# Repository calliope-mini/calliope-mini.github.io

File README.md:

# Technical Documentation

[see here](https://calliope-mini.github.io)

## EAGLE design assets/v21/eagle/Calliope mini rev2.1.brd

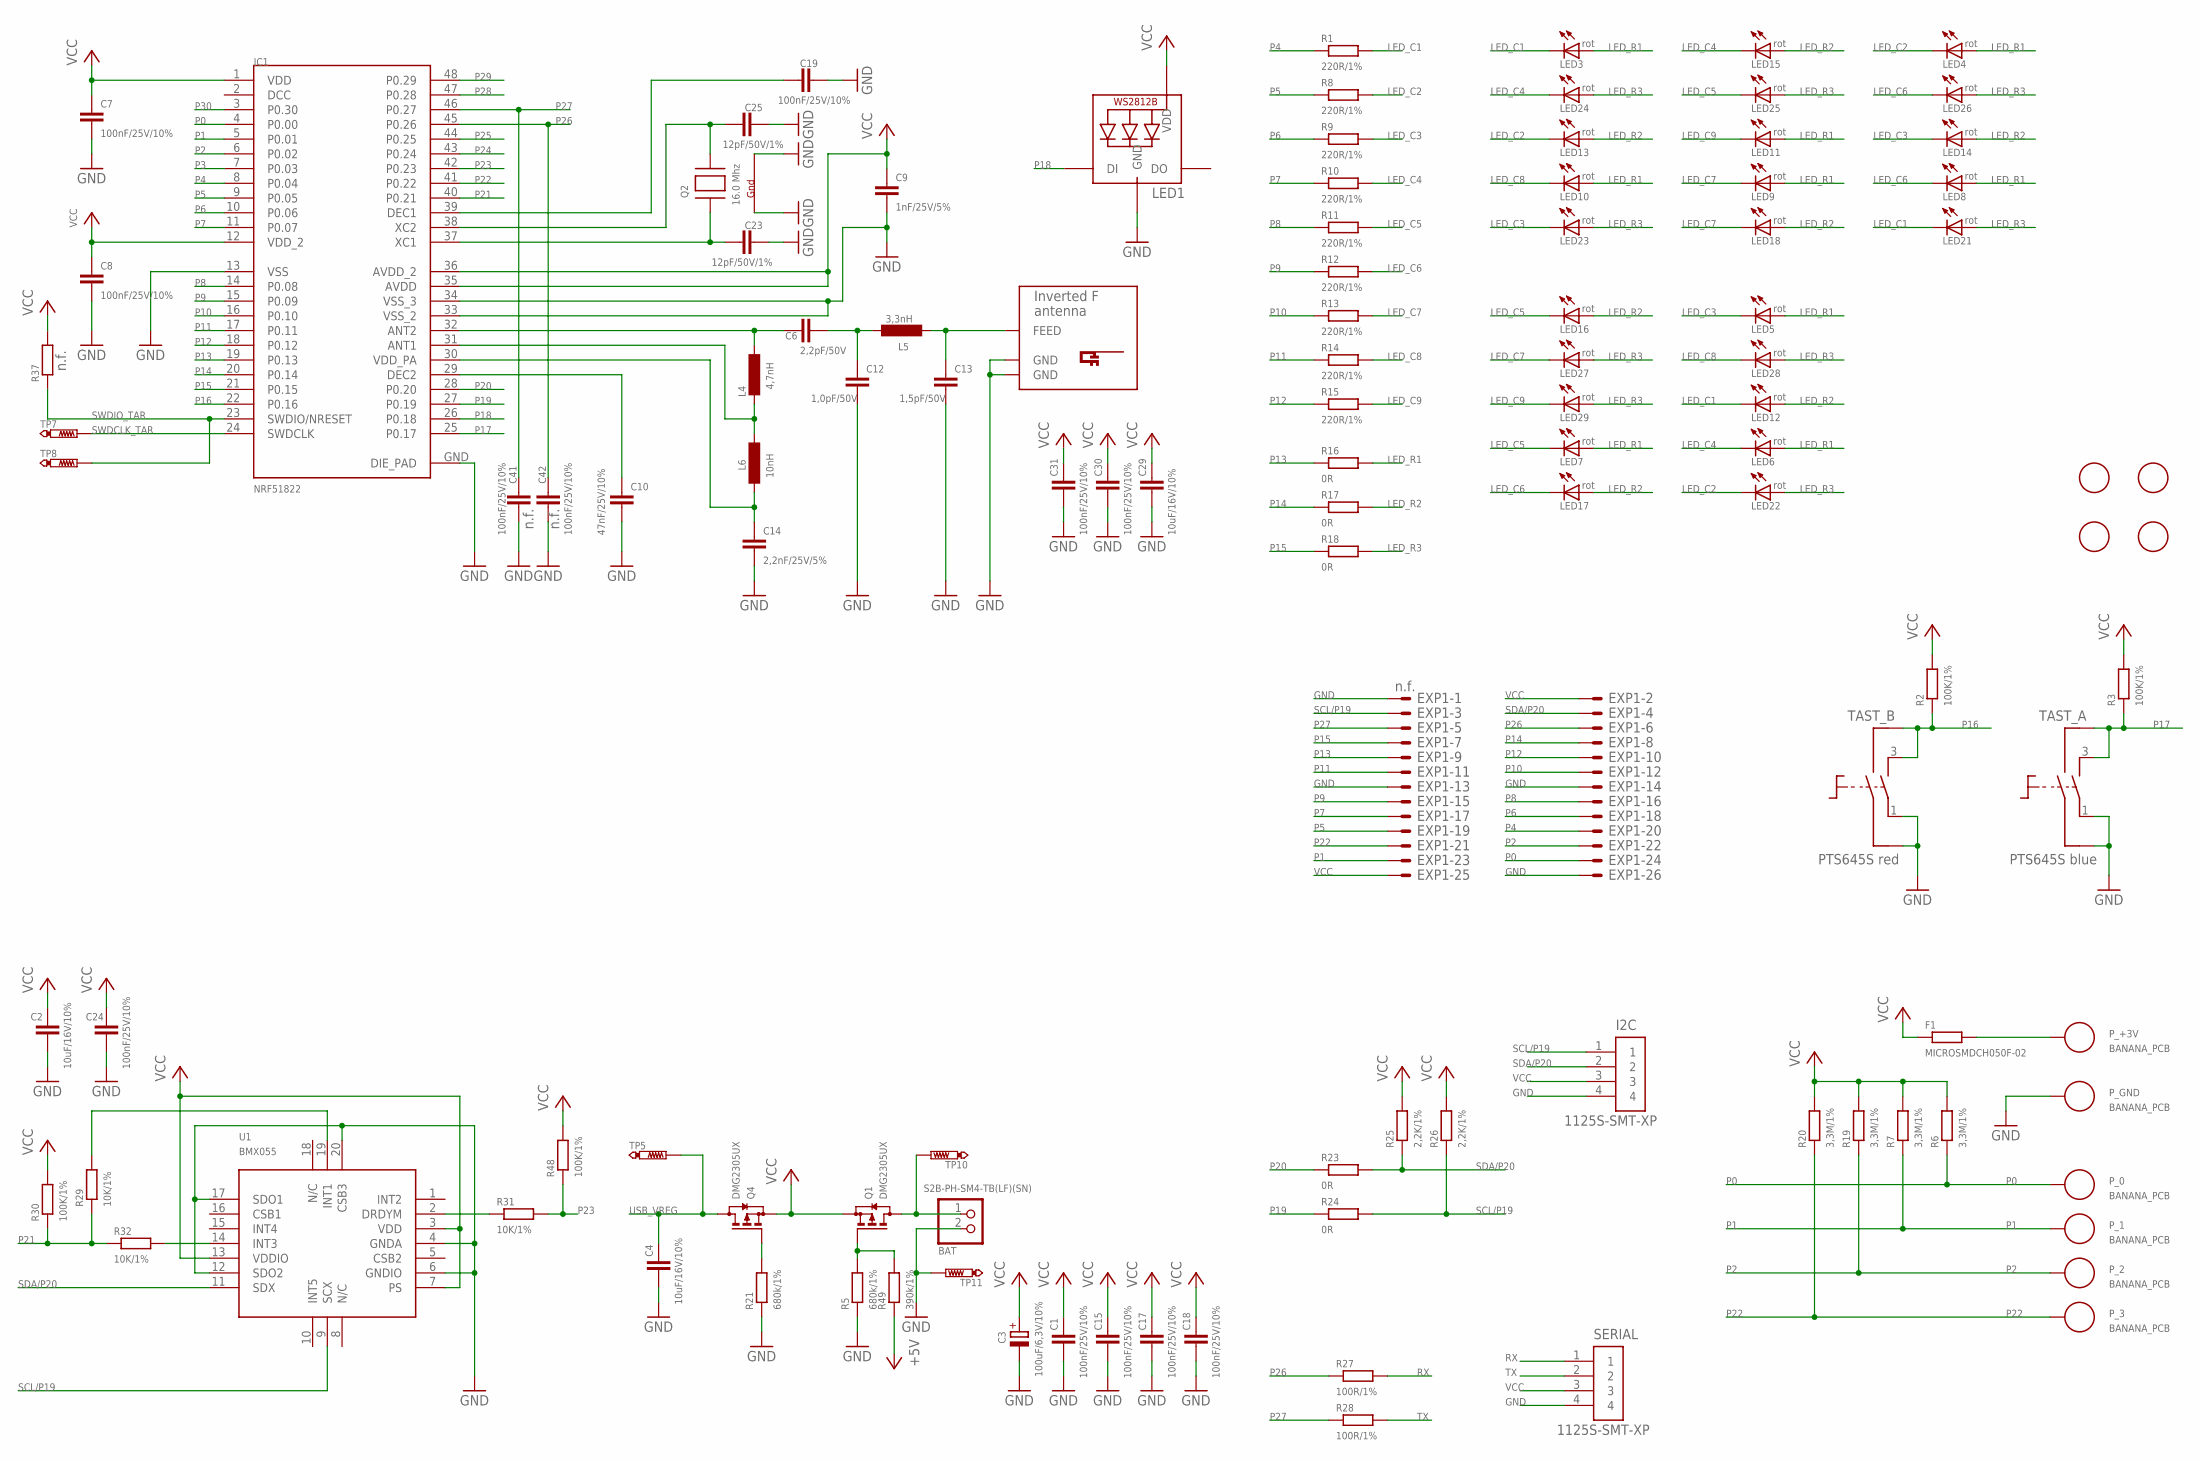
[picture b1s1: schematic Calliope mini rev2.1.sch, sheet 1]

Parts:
BAT: S2B-PH-SM4-TB(LF)(SN); JST-PH-2-SMT-RA
C1, C7, C8, C15, C17, C18, C19, C24, C30, C31, C41, C42: 100nF/25V/10%; 0402
C2, C4, C29: 10uF/16V/10%; 0402
C3: 100uF/6,3V/10%; D/7343-31R
C6: 2,2pF/50V; 0402
C9: 1nF/25V/5%; 0402
C10: 47nF/25V/10%; 0402
C12: 1,0pF/50V; 0402
C13: 1,5pF/50V; 0402
C14: 2,2nF/25V/5%; 0402
C23, C25: 12pF/50V/1%; 0402
EXP1: ML26E; ML26
F1: MICROSMDCH050F-02; R1210
I2C: 1125S-SMT-XP
IC1: NRF51822; QFN48
L4: 4,7nH; 0402
L5: 3,3nH; 0402
L6: 10nH; 0402
LED1: SK6812MINI; LED3535
LED3, LED4, LED5, LED6, LED7, LED8, LED9, LED10, LED11, LED12, LED13, LED14, LED15, LED16, LED17, LED18, LED21, LED22, LED23, LED24, LED25, LED26, LED27, LED28, LED29: rot; CHIPLED_0603
P_0, P_1, P_2, P_3: BANANA_PCB; BANANA_REC
P_+3V: BANANA_PCB; BANANA_REC
P_GND: BANANA_PCB; BANANA_REC
Q1, Q4: DMG2305UX; SOT23
Q2: 16.0 Mhz; NX3225
R1, R8, R9, R10, R11, R12, R13, R14, R15: 220R/1%; 0402
R2, R3, R30, R48: 100K/1%; 0402
R5, R21: 680k/1%; 0402
R6, R7, R19, R20: 3,3M/1%; 0402
R16, R17, R18, R23, R24: 0R; 0402
R25, R26: 2,2K/1%; 0402
R27, R28: 100R/1%; 0402
R29, R31, R32: 10K/1%; 0402
R37: R-EU_0402; 0402
R49: 390k/1%; 0402
SERIAL: 1125S-SMT-XP
TAST_A: PTS645S blue; PTS645S
TAST_B: PTS645S red; PTS645S
TP5, TP7, TP8, TP10, TP11: PTR1B1,27; B1,27
U1: BMX055
U$2: INVERTED_F_ANTENNA; DN0007+0_MIRROR
U$5, U$6, U$7, U$8: FIDUCIAL; FIDUCIAL_1MM

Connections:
+5V: R49.1; also elsewhere on the board
GND: BAT.2 (1), C1.2, C2.2, C3.-, C4.2, C7.2, C8.2, C9.2, C10.2, C12.2, C13.2, C14.2, C15.2, C17.2, C18.2, C19.2, C23.2, C24.2, C25.2, C29.2, C30.2, C31.2, C41.2, C42.2, EXP1.1, EXP1.13, EXP1.14, EXP1.26, I2C.4, IC1.13 (VSS), IC1.33 (VSS_2), IC1.34 (VSS_3), IC1.GND (DIE_PAD), LED1.4 (GND), P_GND.1, Q2.2 (G2), Q2.4 (G1), R5.1, R21.1, SERIAL.4, TAST_A.1, TAST_A.2, TAST_B.1, TAST_B.2, TP11.TP, U1.4 (GNDA), U1.6 (GNDIO), U1.12 (SDO2), U1.17 (SDO1), U1.20 (CSB3), U$2.GND, U$2.GND@1 (GND); also elsewhere on the board
LED_C1: LED3.A, LED12.A, LED21.A, R1.2
LED_C2: LED4.A, LED13.A, LED22.A, R8.2
LED_C3: LED5.A, LED14.A, LED23.A, R9.2
LED_C4: LED6.A, LED15.A, LED24.A, R10.2
LED_C5: LED7.A, LED16.A, LED25.A, R11.2
LED_C6: LED8.A, LED17.A, LED26.A, R12.2
LED_C7: LED9.A, LED18.A, LED27.A, R13.2
LED_C8: LED10.A, LED28.A, R14.2
LED_C9: LED11.A, LED29.A, R15.2
LED_R1: LED3.C, LED4.C, LED5.C, LED6.C, LED7.C, LED8.C, LED9.C, LED10.C, LED11.C, R16.2
LED_R2: LED12.C, LED13.C, LED14.C, LED15.C, LED16.C, LED17.C, LED18.C, R17.2
LED_R3: LED21.C, LED22.C, LED23.C, LED24.C, LED25.C, LED26.C, LED27.C, LED28.C, LED29.C, R18.2
unnamed: C25.1, IC1.38 (XC2), Q2.3 (X2)
unnamed: R29.2, U1.19 (INT1)
unnamed: R32.2, U1.14 (INT3)
unnamed: Q1.1 (G), R5.2, R49.2
unnamed: F1.2, P_+3V.1
unnamed: C23.1, IC1.37 (XC1), Q2.1 (X1)
unnamed: C14.1, IC1.30 (VDD_PA), L6.1
unnamed: C6.1, IC1.32 (ANT2), L4.1
unnamed: C6.2, C12.1, L5.1
unnamed: C13.1, L5.2, U$2.FEED
unnamed: IC1.31 (ANT1), L4.2, L6.2
unnamed: C19.1, IC1.39 (DEC1)
unnamed: Q4.1 (G), R21.2
unnamed: C10.1, IC1.29 (DEC2)
unnamed: R31.1, U1.2 (DRDYM)
P0: EXP1.24, IC1.4 (P0.00), P_0.1, R6.1
P1: EXP1.23, IC1.5 (P0.01), P_1.1, R7.1
P2: EXP1.22, IC1.6 (P0.02), P_2.1, R19.1
P3: IC1.7 (P0.03); also elsewhere on the board
P4: EXP1.20, IC1.8 (P0.04), R1.1
P5: EXP1.19, IC1.9 (P0.05), R8.1
P6: EXP1.18, IC1.10 (P0.06), R9.1
P7: EXP1.17, IC1.11 (P0.07), R10.1
P8: EXP1.16, IC1.14 (P0.08), R11.1
P9: EXP1.15, IC1.15 (P0.09), R12.1
P10: EXP1.12, IC1.16 (P0.10), R13.1
P11: EXP1.11, IC1.17 (P0.11), R14.1
P12: EXP1.10, IC1.18 (P0.12), R15.1
P13: EXP1.9, IC1.19 (P0.13), R16.1
P14: EXP1.8, IC1.20 (P0.14), R17.1
P15: EXP1.7, IC1.21 (P0.15), R18.1
P16: IC1.22 (P0.16), R2.1, TAST_B.3 (S1), TAST_B.4 (S2)
P17: IC1.25 (P0.17), R3.1, TAST_A.3 (S1), TAST_A.4 (S2)
P18: IC1.26 (P0.18), LED1.1 (DI)
P19: IC1.27 (P0.19), R24.1
P20: IC1.28 (P0.20), R23.1
P21: IC1.40 (P0.21), R29.1, R30.1, R32.1
P22: EXP1.21, IC1.41 (P0.22), P_3.1, R20.1
P23: IC1.42 (P0.23), R31.2, R48.1
P24: IC1.43 (P0.24); also elsewhere on the board
P25: IC1.44 (P0.25); also elsewhere on the board
P26: C42.1, EXP1.6, IC1.45 (P0.26), R27.1
P27: C41.1, EXP1.5, IC1.46 (P0.27), R28.1
P28: IC1.47 (P0.28); also elsewhere on the board
P29: IC1.48 (P0.29); also elsewhere on the board
P30: IC1.3 (P0.30); also elsewhere on the board
RX: R27.2, SERIAL.1
SCL/P19: EXP1.3, I2C.1, R24.2, R26.1, U1.9 (SCX)
SDA/P20: EXP1.4, I2C.2, R23.2, R25.1, U1.11 (SDX)
SWDCLK_TAR: IC1.24 (SWDCLK), TP7.TP; also elsewhere on the board
SWDIO_TAR: IC1.23 (SWDIO/NRESET), R37.1, TP8.TP; also elsewhere on the board
TX: R28.2, SERIAL.2
USB_VREG: C4.1, Q4.3 (D), TP5.TP; also elsewhere on the board
VCC: C1.1, C2.1, C3.+, C7.1, C8.1, C9.1, C15.1, C17.1, C18.1, C24.1, C29.1, C30.1, C31.1, EXP1.2, EXP1.25, F1.1, I2C.3, IC1.1 (VDD), IC1.12 (VDD_2), IC1.35 (AVDD), IC1.36 (AVDD_2), LED1.2 (VDD), Q1.2 (S), Q4.2 (S), R2.2, R3.2, R6.2, R7.2, R19.2, R20.2, R25.2, R26.2, R30.2, R37.2, R48.2, SERIAL.3, U1.3 (VDD), U1.7 (PS), U1.13 (VDDIO); also elsewhere on the board
VIN: BAT.1 (2), Q1.3 (D), TP10.TP

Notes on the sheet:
LED1

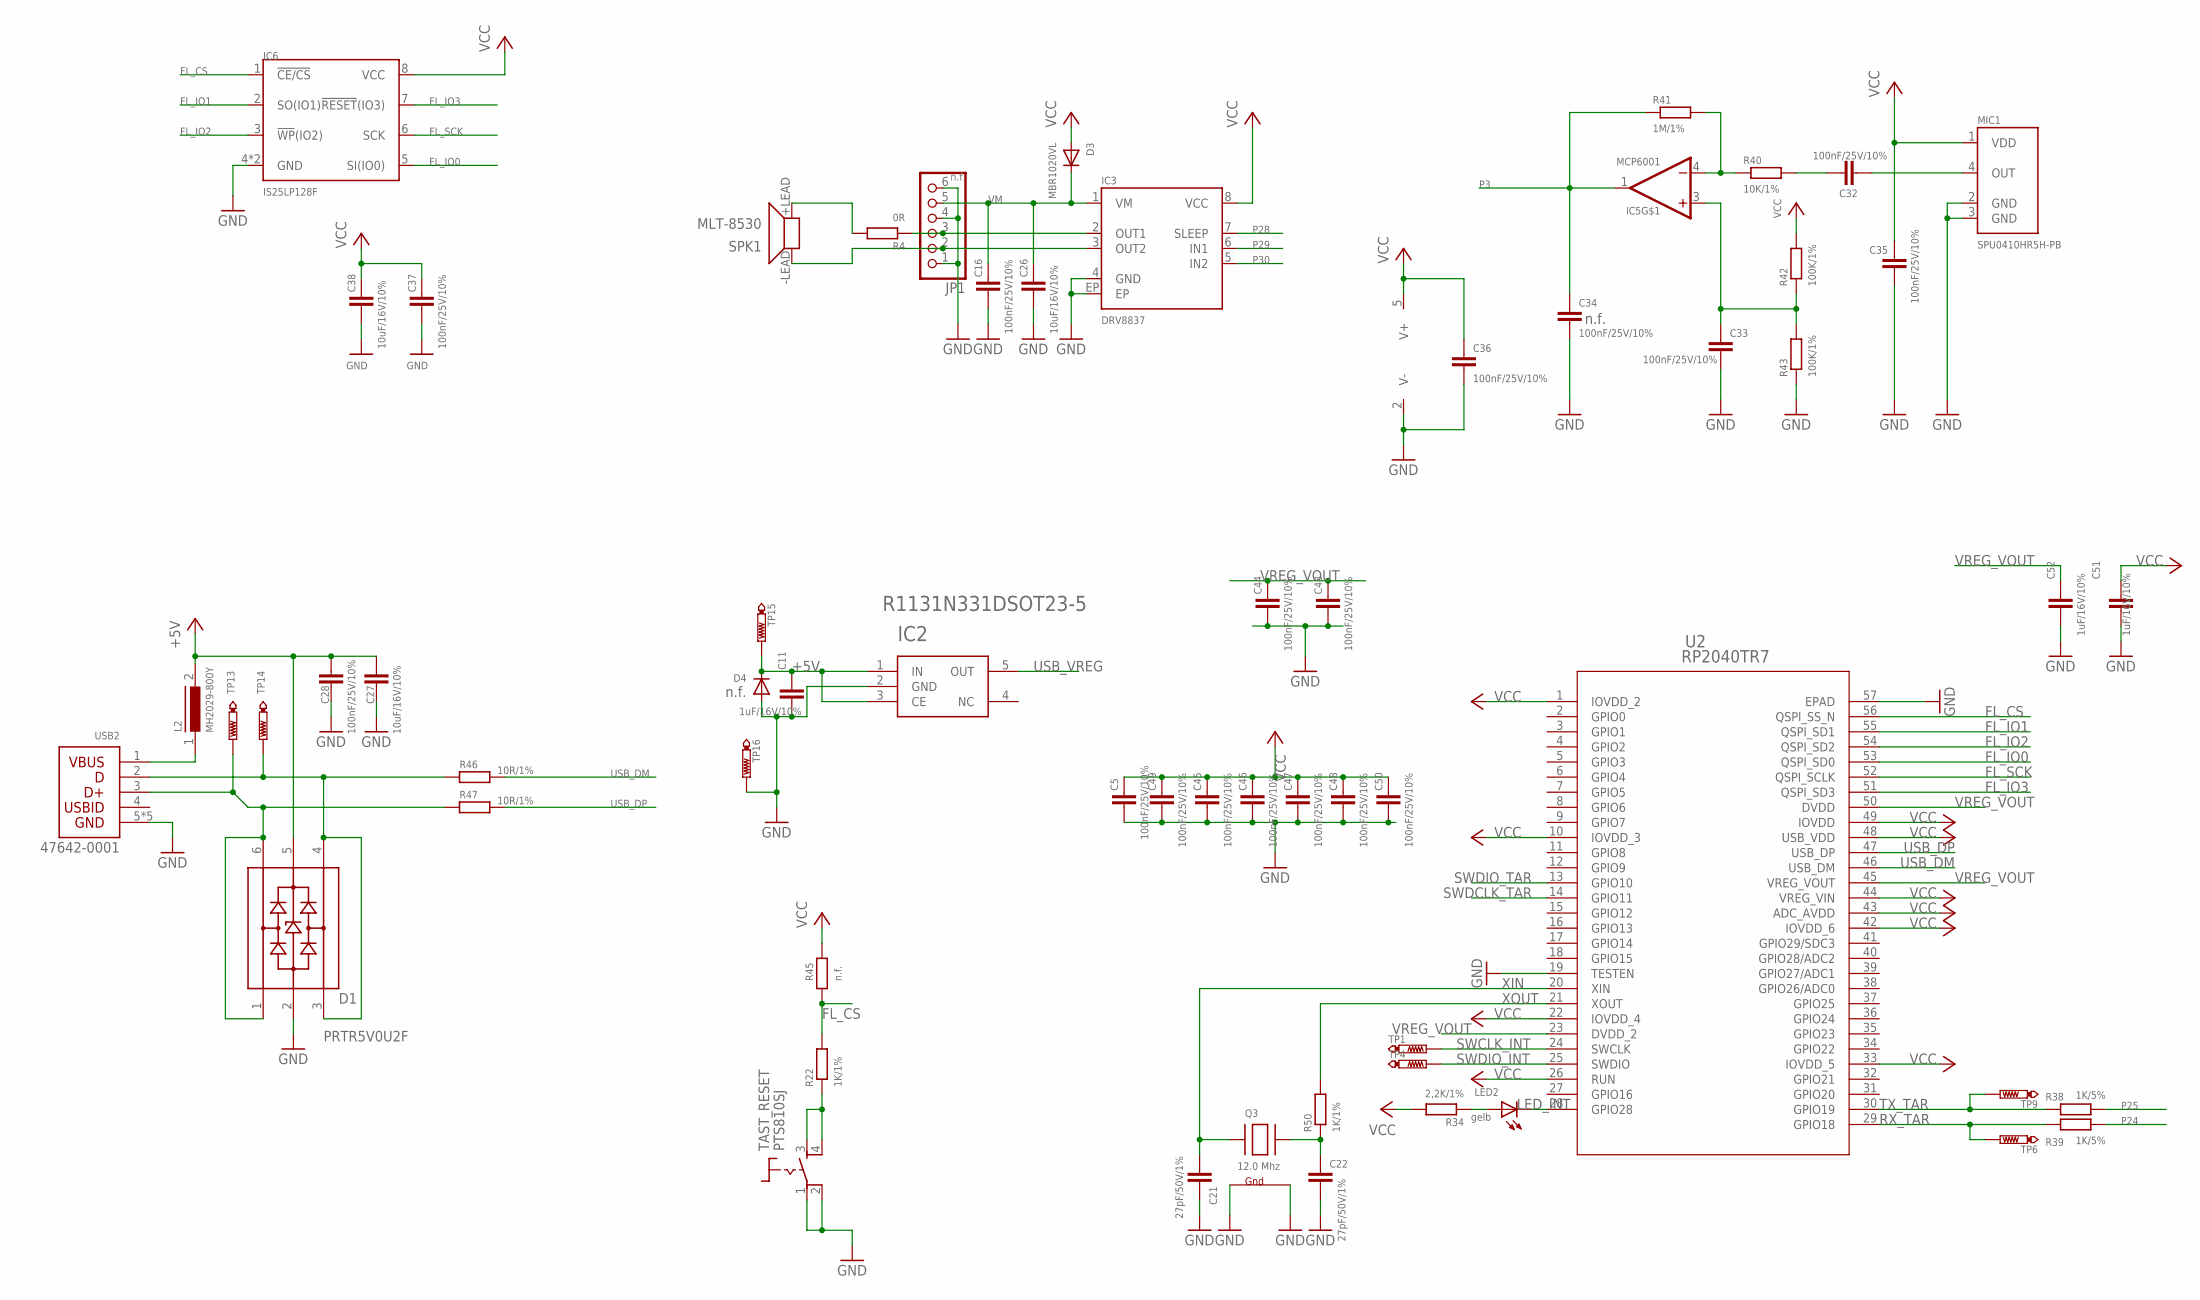
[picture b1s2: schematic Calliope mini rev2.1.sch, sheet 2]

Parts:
C5, C16, C28, C32, C33, C34, C35, C36, C37, C43, C44, C45, C46, C47, C48, C49, C50: 100nF/25V/10%; 0402
C11, C51, C52: 1uF/16V/10%; 0402
C21, C22: 27pF/50V/1%; 0402
C26, C27, C38: 10uF/16V/10%; 0402
D1: PRTR5V0U2F; SOT886
D3: MBR1020VL; SOD-123FL
D4: DIODE-SOD323-R; SOD323-R
IC2: R1131N331DSOT23-5; SOT23-5
IC3: DRV8837; WSON8
IC5: MCP6001; SOT23-5
IC6: IS25LP128F; VQFN8_6X5
JP1: PINHD-1X6-OFF; 1X06-OFF
L2: MH2029-800Y; FERRIT_0805
LED2: gelb; CHIPLED_0603
MIC1: SPU0410HR5H-PB
Q3: 12.0 Mhz; NX3225
R4: 0R; 0402
R22, R50: 1K/1%; 0402
R34: 2,2K/1%; 0402
R38, R39: 1K/5%; 0402
R40: 10K/1%; 0402
R41: 1M/1%; 0402
R42, R43: 100K/1%; 0402
R45: n.f.; 0402
R46, R47: 10R/1%; R0402
SPK1: MLT-8530
TAST_RESET: PTS810SJ; PTS810
TP1, TP4, TP6, TP9, TP13, TP14, TP15, TP16: PTR1B1,27; B1,27
U2: RP2040TR7; RP2040TR7_RPI
USB2: 47642-0001

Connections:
+5V: C11.1, C27.1, C28.1, D1.5, D4.C, IC2.1 (IN), IC2.3 (CE), L2.2, TP15.TP; also elsewhere on the board
FL_CS: IC6.1 (!CE/CS), R22.2, R45.1, U2.56 (QSPI_SS_N)
FL_IO0: IC6.5 (SI(IO0)), U2.53 (QSPI_SD0)
FL_IO1: IC6.2 (SO(IO1)), U2.55 (QSPI_SD1)
FL_IO2: IC6.3 (!WP!(IO2)), U2.54 (QSPI_SD2)
FL_IO3: IC6.7 (!RESET!(IO3)), U2.51 (QSPI_SD3)
FL_SCK: IC6.6 (SCK), U2.52 (QSPI_SCLK)
GND: C5.2, C11.2, C16.2, C21.2, C22.2, C26.2, C27.2, C28.2, C33.2, C34.2, C35.2, C36.2, C37.2, C38.2, C43.2, C44.2, C45.2, C46.2, C47.2, C48.2, C49.2, C50.2, C51.2, C52.2, D1.2, D4.A, IC2.2 (GND), IC3.4 (GND), IC3.EP, IC5.2 (V-), IC6.4 (GND), IC6.EP (GND), JP1.1, JP1.4, JP1.6, MIC1.2 (GND), MIC1.3 (GND), Q3.2 (G2), Q3.4 (G1), R43.1, TAST_RESET.1, TAST_RESET.2 (P1), TP16.TP, U2.19 (TESTEN), U2.57 (EPAD), USB2.5, USB2.P$1 (5), USB2.P$2 (5), USB2.P$3 (5), USB2.P$4 (5); also elsewhere on the board
LED_INT: LED2.A, U2.28 (GPIO28)
unnamed: IC3.3 (OUT2), JP1.2, SPK1.-LEAD (1)
unnamed: LED2.C, R34.1
unnamed: IC3.2 (OUT1), JP1.3, R4.1
unnamed: C22.1, Q3.3 (X2), R50.1
unnamed: R4.2, SPK1.+LEAD (2)
unnamed: C33.1, IC5.3 (+IN), R42.1, R43.2
unnamed: L2.1, USB2.1
unnamed: D1.1, D1.6, R47.1, TP13.TP, USB2.3
unnamed: D1.3, D1.4, R46.1, TP14.TP, USB2.2
unnamed: IC5.4 (-IN), R40.1, R41.2
unnamed: C32.1, R40.2
unnamed: C32.2, MIC1.4 (OUT)
P3: C34.1, IC5.1 (OUT), R41.1; also elsewhere on the board
P24: R39.2; also elsewhere on the board
P25: R38.2; also elsewhere on the board
P28: IC3.7 (SLEEP); also elsewhere on the board
P29: IC3.6 (IN1); also elsewhere on the board
P30: IC3.5 (IN2); also elsewhere on the board
RESET_SW: R22.1, TAST_RESET.3 (S), TAST_RESET.4 (S1)
RX_TAR: R39.1, TP6.TP, U2.29 (GPIO18)
SWCLK_INT: TP1.TP, U2.24 (SWCLK)
SWDCLK_TAR: U2.14 (GPIO11); also elsewhere on the board
SWDIO_INT: TP4.TP, U2.25 (SWDIO)
SWDIO_TAR: U2.13 (GPIO10); also elsewhere on the board
TX_TAR: R38.1, TP9.TP, U2.30 (GPIO19)
USB_DM: R46.2, U2.46 (USB_DM)
USB_DP: R47.2, U2.47 (USB_DP)
USB_VREG: IC2.5 (OUT); also elsewhere on the board
VCC: C5.1, C35.1, C36.1, C37.1, C38.1, C45.1, C46.1, C47.1, C48.1, C49.1, C50.1, C51.1, D3.A, IC3.8 (VCC), IC5.5 (V+), IC6.8 (VCC), MIC1.1 (VDD), R34.2, R42.2, R45.2, U2.1 (IOVDD_2), U2.10 (IOVDD_3), U2.22 (IOVDD_4), U2.26 (RUN), U2.33 (IOVDD_5), U2.42 (IOVDD_6), U2.43 (ADC_AVDD), U2.44 (VREG_VIN), U2.48 (USB_VDD), U2.49 (IOVDD); also elsewhere on the board
VM: C16.1, C26.1, D3.C, IC3.1 (VM), JP1.5
VREG_VOUT: C43.1, C44.1, C52.1, U2.23 (DVDD_2), U2.45 (VREG_VOUT), U2.50 (DVDD)
XIN: C21.1, Q3.1 (X1), U2.20 (XIN)
XOUT: R50.2, U2.21 (XOUT)

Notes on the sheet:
n.f.

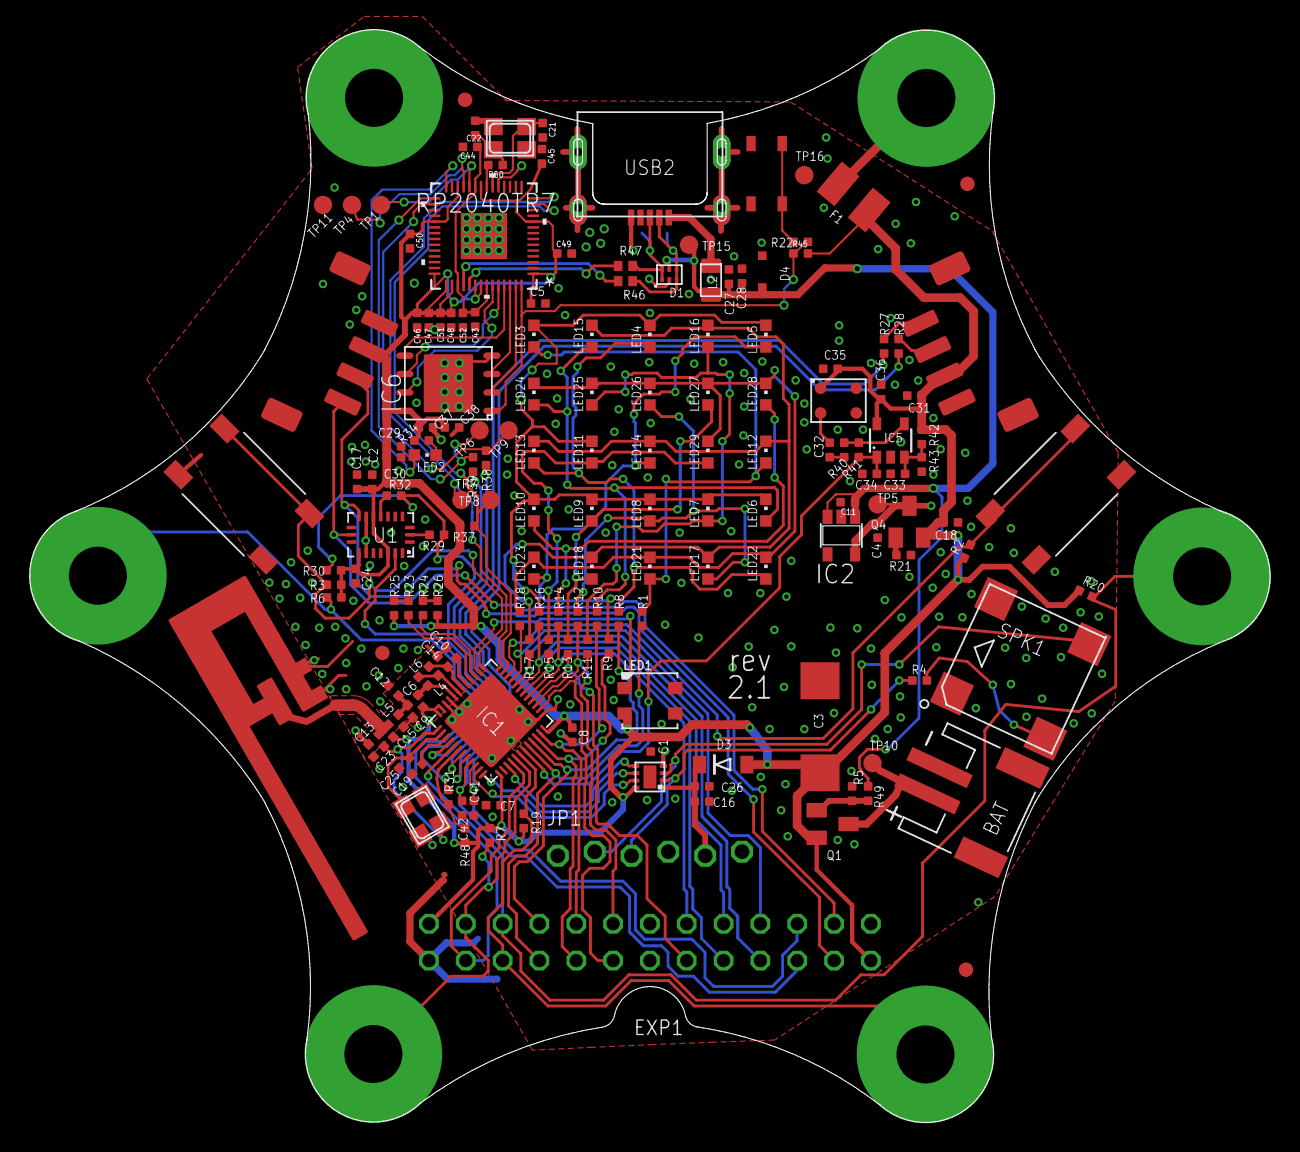
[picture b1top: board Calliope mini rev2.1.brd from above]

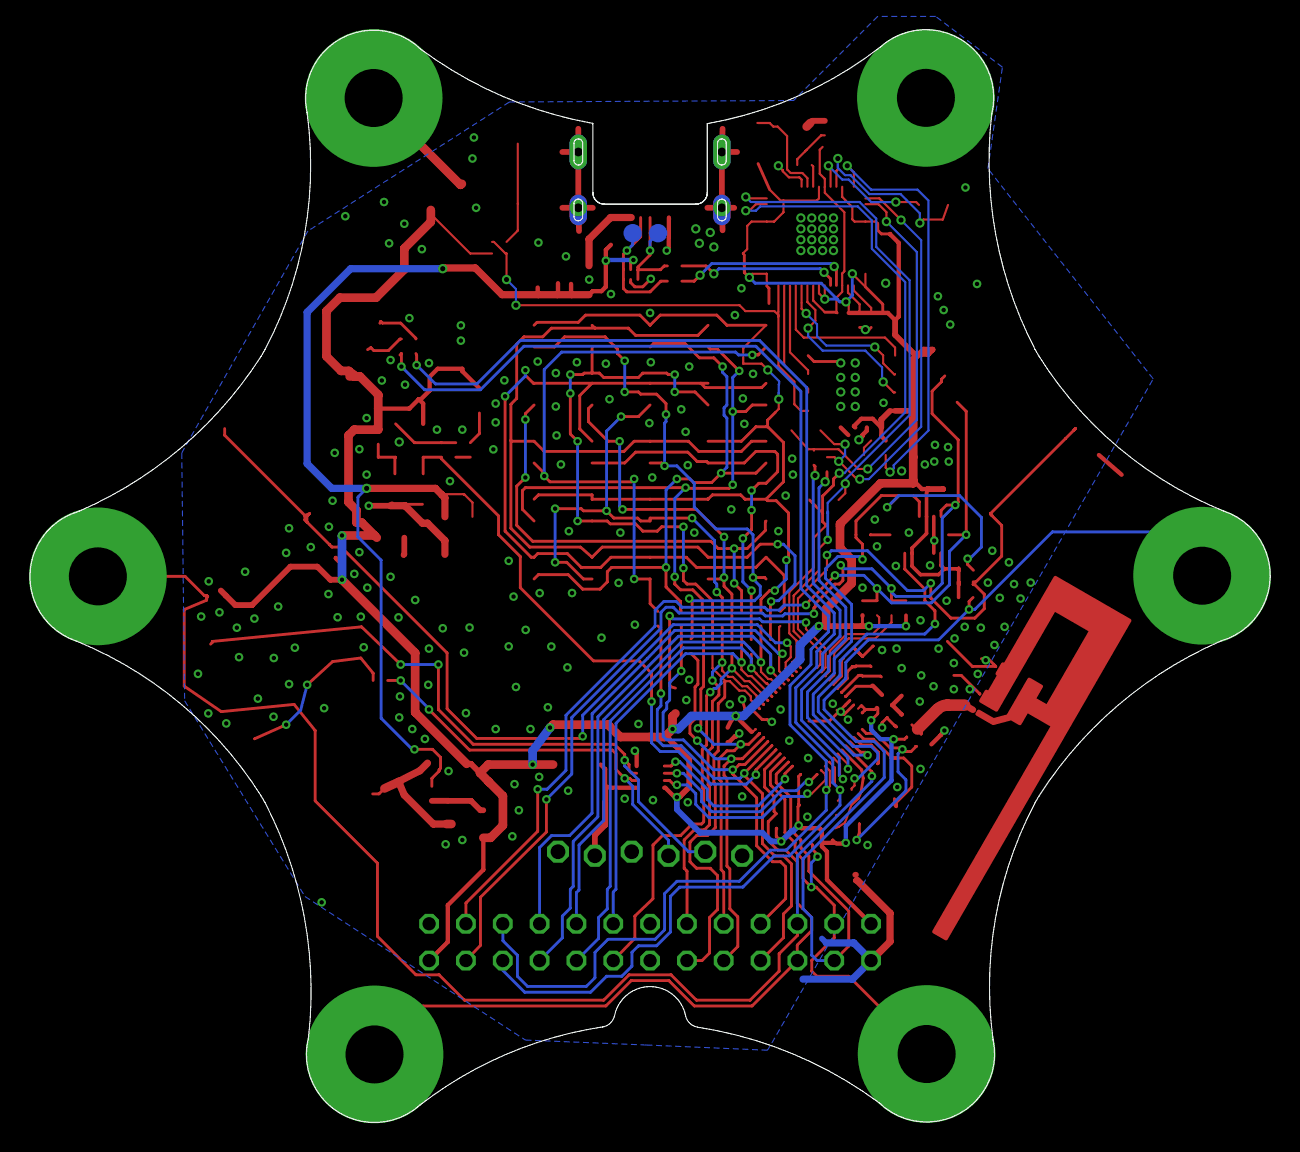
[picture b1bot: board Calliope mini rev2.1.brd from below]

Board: 2 copper layers, 85.5 x 75.4 mm, 176 parts (3 on the bottom side), 99 nets.

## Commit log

2017-04-13 Set theme jekyll-theme-slate
2017-04-13 test
2017-04-13 update with own data
2017-04-13 fix build process
2017-04-13 fix missing link
2017-04-13 fix link
2017-04-20 update corrected block schaltbild
2017-04-20 update links on images
2017-04-20 fix responsive width
2017-04-20 use github theming
2017-04-21 fix link to schema
2017-07-21 fix png link, add errata
2017-07-21 fixed file to contain second page
2017-07-21 fix unneccessary subtext in schema
2017-07-21 fix typo
2017-11-05 Bills of Materials for v1.0 CSV HTML TXT
2018-03-16 new version v1.3
2018-03-19 v1.3 pinout
2020-08-28 Updated for REV2
    Added the new version
2020-10-23 Updated license information
    License information
2020-10-23 Update
    Update
2020-10-23 Updated information
    Update
2021-03-29 Updated Bootloader-link
    Updated Bootloader-link
2022-02-28 Update page 02
    Added page 02
2022-10-26 Updated for changes on 2.1
2022-10-26 Updated path to correct image
2023-12-04 Update Calliope mini 3
2023-12-05 Deleted Text to missing Image (for now)
2023-12-05 INtegrated Jacdac Text
2023-12-05 Fixed typo

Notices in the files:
parts and their libraries:
COPYRIGHT: Copyright (C) 2022 Ultra Librarian. All rights reserved.
